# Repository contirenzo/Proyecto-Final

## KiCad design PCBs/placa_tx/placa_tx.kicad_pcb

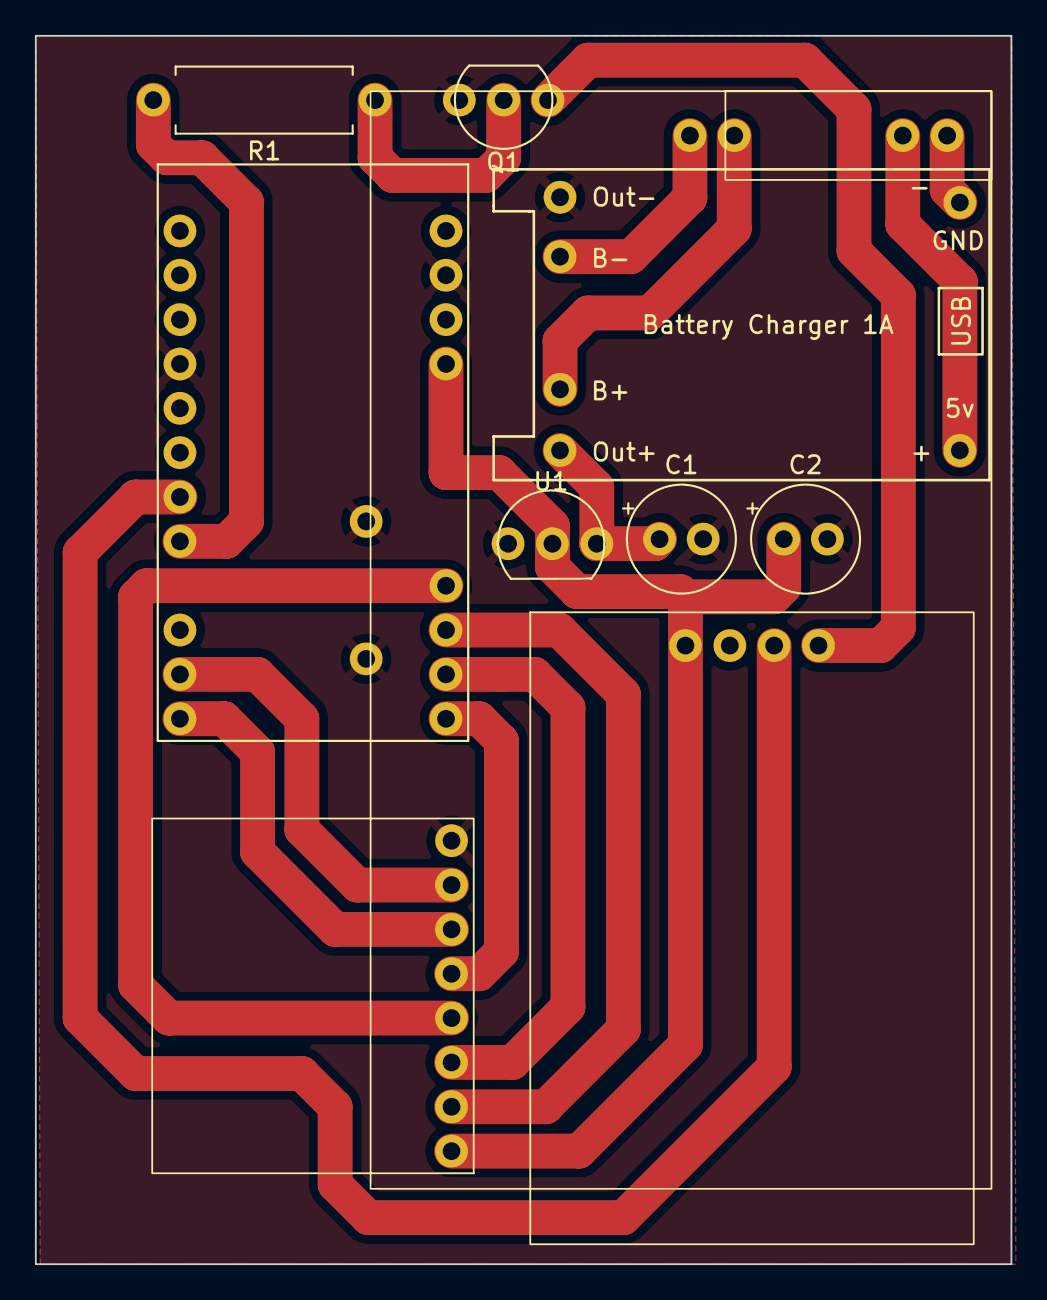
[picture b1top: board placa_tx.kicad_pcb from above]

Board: 2 copper layers, 55.9 x 70.4 mm, 11 parts (0 on the bottom side), 17 nets.

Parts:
C1, C2: C; CP_Radial_Tantal_D6.0mm_P2.50mm
LiPo3.7v1: LiPo Battery
LoRaSX1: LoRaSx1278
Neo-6m1: Neo-6m
ProMini1: MODULE_ARDUINO_PRO_MINI
Q1: BC337; TO-92_Inline
R1: R; R_Axial_DIN0411_L9.9mm_D3.6mm_P12.70mm_Horizontal
TP1: TP4056
U1: AMS1117-3.3; TO-92L_Inline
panelSolar1: solar panel

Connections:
GND: C1.2, C2.2, LoRaSX1.8 (GND), ProMini1.4 (GND), ProMini1.20 (GND), Q1.3 (E), TP1.6 (OUT-), U1.1 (GND)
unnamed: LiPo3.7v1.1 (+), TP1.5 (B-)
unnamed: LiPo3.7v1.2 (-), TP1.4 (B+)
unnamed: LoRaSX1.6 (DI00), ProMini1.12 (9)
unnamed: LoRaSX1.2 (MISO), ProMini1.28 (MISO)
unnamed: LoRaSX1.3 (MOSI), ProMini1.29 (MOSI)
unnamed: LoRaSX1.5 (NSS), ProMini1.30 (SS)
unnamed: LoRaSX1.7 (REST), ProMini1.11 (8)
unnamed: LoRaSX1.4 (SLK), ProMini1.27 (SCK)
unnamed: Neo-6m1.4 (GND), Q1.1 (C)
unnamed: Neo-6m1.3 (TX), ProMini1.7 (4)
unnamed: ProMini1.8 (5), R1.2
unnamed: Q1.2 (B), R1.1
unnamed: TP1.1 (5V), panelSolar1.1 (5V)
unnamed: TP1.2 (GND), panelSolar1.2 (GND)
unnamed: C1.1, TP1.3 (OUT+), U1.3 (VI)
VCC: C2.1, LoRaSX1.1 (VCC), Neo-6m1.1 (VCC), ProMini1.22 (VCC1), U1.2 (VO)

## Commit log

2024-09-10 Agrego códigos
2024-09-10 Agrego archivos skp
2024-09-10 Agrego archivos pcb
2024-09-11 Comento códigos
2024-09-12 Arreglo codigos
